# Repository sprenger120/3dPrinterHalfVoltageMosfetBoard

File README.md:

# 3D Printer Half Voltage MOSFET Board
Makes 12V Heaters (Bed + Extruder) compatible with 24V by plugging in between your 3D Printer's motherboard and your heating elements. 
The board contains **overheat protection** and will leave the heaters off regardless of what the 3D printer wants. When your printer is configured correctly a thermal runaway error should stop the machine.
The firmware also allows you to finely control how much voltage you want to send to your heaters if the 50% reduction isn't enough or you want to boost performance slightly.

### Making one

This project is mostly built from stuff I had laying around so make changes according to what you had laying around. *Capacitors with a higher voltage but the same farads rating are always compatible!*  

You can find the PCB's gerber files in fab/.

- 1x 10uF 36V MLCC , 0805 (imperial) 
- 3x 2.2uF 16V MLCC, 0603 (imperial) 
- 3x 1uF 36V MLCC, 0805 (imperial) 
- 7x 100nF 16V MLCC, 0603 (imperial) 
- 4x 100uF 35V Al-Poly Capacitor, 10x12mm
- 2x Green LED, 0603 (imperial)
- 1x ESDCAN01-2BLY TVS diode (optional if you like to live "dangerously")
- 2x Phoenix 1987740 Screw Terminal 32A (select something equivalent, these have a wierd orientation)
- 1x Phoenix 1729018 Screw Terminal 10A (or just solder wires, this is for signal only)
- 2x Vishay SiSA88DN N-Ch Enh. MOSFET
- 4x 20k Ohm Resistor, 0603 (imperial)
- 2x 300 Ohm Resistor, 0603 (imperial)
- 3x 10k Ohm Resistor, 0603 (imperial)
- 2x 10 Ohm Resistor, 0603 (imperial)
- 2x 100k Ohm Resistor, 0603 (imperial)
- 1x 10k Ohm NTC Thermistor, 0603 (imperial) (Panasonic ERT-J1VG103JA or equivalent)
- 1x STM32L011F3P Microcontroller
- 1x MCP1703A-3302 3.3V fixed linear regulator
- 1x XC6702-3.3 12V fixed linear regulator
- 1x MIC4126 MOSFET driver

Get a cheap STLINK off of ebay and hook up the pins of the J_SWD connector to it.

**todo swd port pinout**, **todo flash manual**

### Wiring 

- Connect your power supplies' 24V directly to one of the GND, 24V pairs on the left side. Connect the other GND, 24V pair to your motherboard. They are internally bridged. You may use thinner wiring for this connection as your 3D Printer's motherboard now consumes way less power. 
- Connect your heated bed to Heater1+ and Heater1- and your extruder to Heater 2+ and -. Polarity doesn't matter as heaters are just resistors. 
- Connect the **negative** side of your 3D printer's heated bed power output to "Signal Heater 1". Do the same for the extruder output and "Signal Heater 2". 

You have to connect the "Signal Heater" pins to the negative side as virtually all 3D printer motherboards don't switch the plus side but rather switch the negative side. If you would connect the the "Signal Heater" pins to the positive side the board the heaters will stay off permanently.

**todo rev. 1 testing**

### Revisions

- Rev. 2
   - Secured "Signal Heater" inputs against accidental 24V connection
- Rev. 1 (Initial release)

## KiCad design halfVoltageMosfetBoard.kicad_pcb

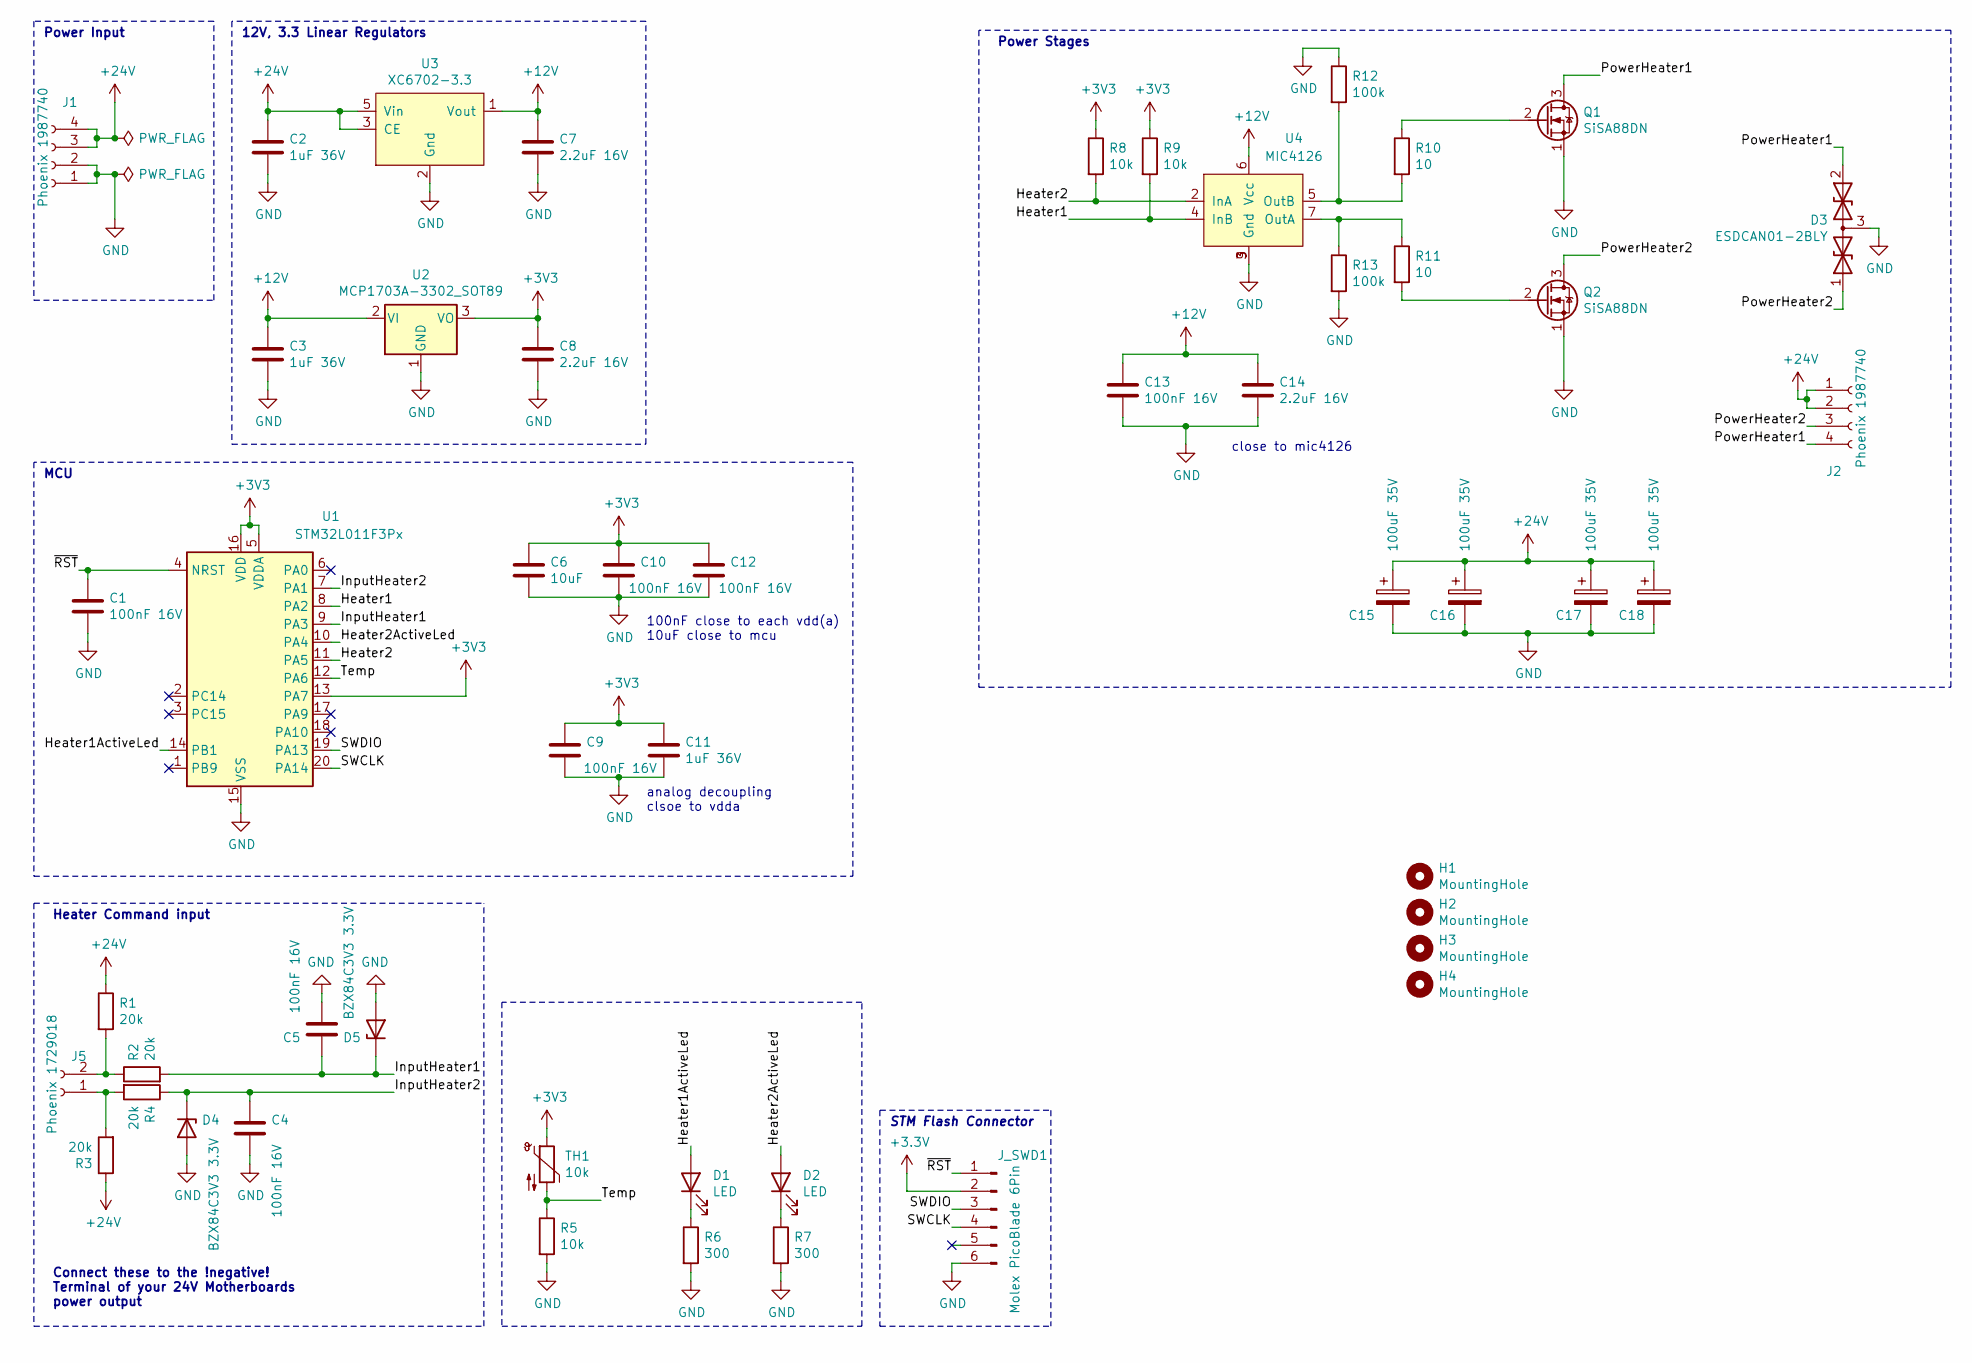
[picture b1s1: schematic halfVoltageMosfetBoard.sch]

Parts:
C1, C4, C5, C9, C10, C12, C13: 100nF 16V; C_0603_1608Metric
C2, C3, C11: 1uF 36V; C_0805_2012Metric
C6: 10uF; C_0805_2012Metric
C7, C8, C14: 2.2uF 16V; C_0603_1608Metric
C15, C16, C17, C18: 100uF 35V; CP_Elec_10x12.5
D1, D2: LED; LED_0603_1608Metric
D3: ESDCAN01-2BLY; SOT-23
D4, D5: BZX84C3V3 3.3V; D_SOT-23_ANK
H1, H2, H3, H4: MountingHole; MountingHole_3.5mm
J1, J2: Phoenix 1987740; TerminalBlock_Phoenix_PT-1,5-4-5.0-H_1x04_P5.00mm_Horizontal
J5: Phoenix 1729018; TerminalBlock_Phoenix_PT-1,5-2-5.0-H_1x02_P5.00mm_Horizontal
J_SWD1: Molex PicoBlade 6Pin; Molex_PicoBlade_53047-0610_1x06_P1.25mm_Vertical
Q1, Q2: SiSA88DN; Vishay_PowerPAK_1212-8_Single
R1, R2, R3, R4: 20k; R_0603_1608Metric
R5, R8, R9: 10k; R_0603_1608Metric
R6, R7: 300; R_0603_1608Metric
R10, R11: 10; R_0603_1608Metric
R12, R13: 100k; R_0603_1608Metric
TH1: 10k; R_0603_1608Metric
U1: STM32L011F3Px; TSSOP-20_4.4x6.5mm_P0.65mm
U2: MCP1703A-3302_SOT89; SOT-89-3
U3: XC6702-3.3; SOT-89-5
U4: MIC4126; SOIC-8-1EP_3.9x4.9mm_P1.27mm_EP2.29x3mm_ThermalVias

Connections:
+12V: C3.1, C7.1, C13.1, C14.1, U2.2 (VI), U3.1 (Vout), U4.6 (Vcc)
+24V: C2.1, C15.1, C16.1, C17.1, C18.1, J1.3, J1.4, J2.1, J2.2, R1.1, R3.1, U3.3 (CE), U3.5 (Vin)
/Heater1: R9.2, U1.8 (PA2), U4.4 (InB)
/Heater1ActiveLed: D1.2 (A), U1.14 (PB1)
/Heater2: R8.2, U1.11 (PA5), U4.2 (InA)
/Heater2ActiveLed: D2.2 (A), U1.10 (PA4)
/InputHeater1: C5.1, D5.1 (K), R2.2, U1.9 (PA3)
/InputHeater2: C4.1, D4.1 (K), R4.1, U1.7 (PA1)
/PowerHeater1: D3.2 (A2), J2.4, Q1.3 (D)
/PowerHeater2: D3.1 (A1), J2.3, Q2.3 (D)
/SWCLK: J_SWD1.4, U1.20 (PA14)
/SWDIO: J_SWD1.3, U1.19 (PA13)
/Temp: R5.1, TH1.2, U1.12 (PA6)
/~RST: C1.1, J_SWD1.1, U1.4 (NRST)
GND: C1.2, C2.2, C3.2, C4.2, C5.2, C6.2, C7.2, C8.2, C9.2, C10.2, C11.2, C12.2, C13.2, C14.2, C15.2, C16.2, C17.2, C18.2, D3.3 (common), D4.2 (A), D5.2 (A), J1.1, J1.2, J_SWD1.6, Q1.1 (S), Q2.1 (S), R5.2, R6.2, R7.2, R12.1, R13.2, U1.15 (VSS), U2.1 (GND), U3.2 (Gnd), U4.3 (Gnd), U4.9 (Gnd)
unnamed: D1.1 (K), R6.1
unnamed: D2.1 (K), R7.1
unnamed: J5.1, R3.2, R4.2
unnamed: J5.2, R1.2, R2.1
unnamed: Q1.2 (G), R10.1
unnamed: Q2.2 (G), R11.2
unnamed: R10.2, R12.2, U4.5 (OutB)
unnamed: R11.1, R13.1, U4.7 (OutA)

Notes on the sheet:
close to mic4126
STM Flash Connector
Power Input
12V, 3.3 Linear Regulators
Power Stages
analog decoupling clsoe to vdda
100nF close to each vdd(a) 10uF close to mcu
MCU
Connect these to the !negative! Terminal of your 24V Motherboards power output
Heater Command input

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
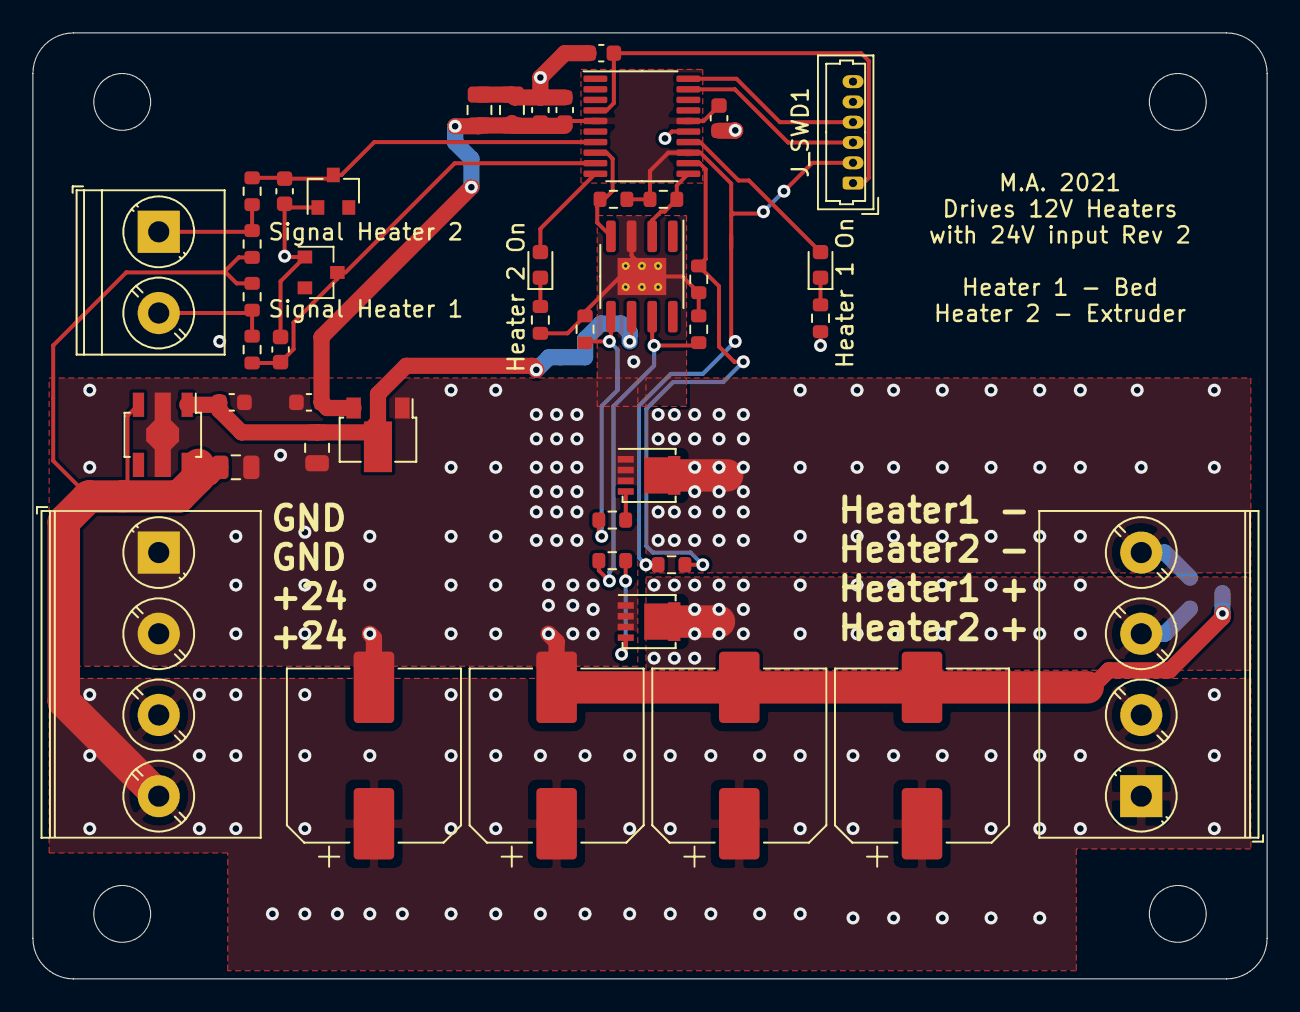
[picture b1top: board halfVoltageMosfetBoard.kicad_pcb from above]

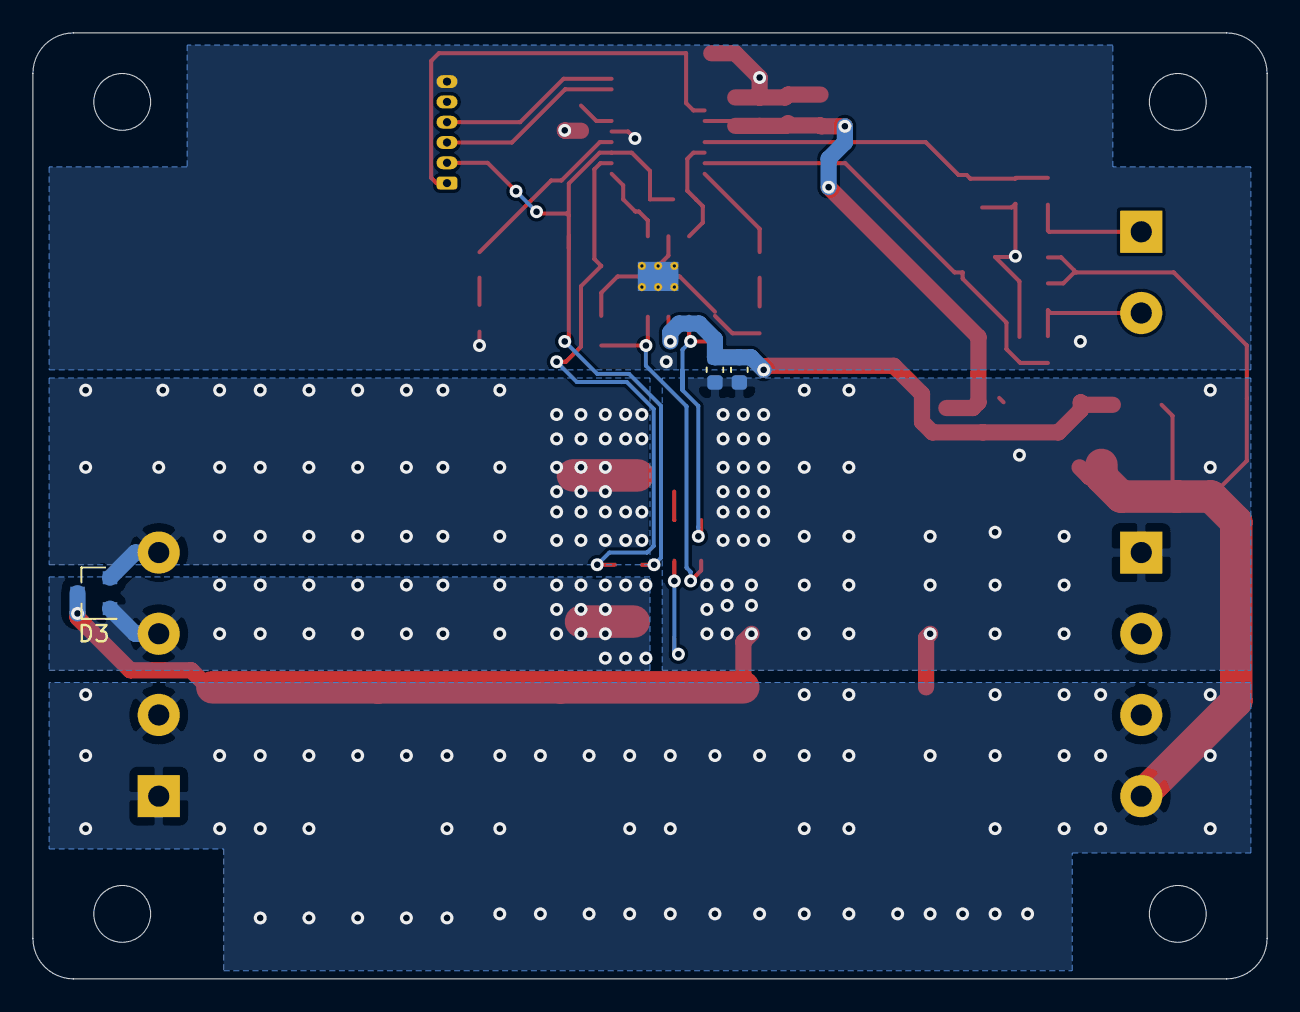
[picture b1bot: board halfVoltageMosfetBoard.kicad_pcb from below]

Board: 2 copper layers, 76.0 x 58.2 mm, 51 parts (3 on the bottom side), 24 nets.

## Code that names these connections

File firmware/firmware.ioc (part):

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Mcu.Name=STM32L011F(3-4)Px
Mcu.Package=TSSOP20
Mcu.UserName=STM32L011F3Px
PA13.Mode=Serial_Wire
PA13.Signal=SYS_SWDIO
PA14.Mode=Serial_Wire
PA14.Signal=SYS_SWCLK
PA2.Signal=S_TIM21_CH1
PA5.Signal=S_TIM2_CH1
PA6.Mode=IN6
PA6.Signal=ADC_IN6
RCC.HSE_VALUE=8000000
RCC.SYSCLKFreq_VALUE=2097000
board=custom

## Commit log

2021-05-12 finished schematic
2021-05-12 finished layout rev A
2021-05-12 Revision 2 changes see readme Added text to readme Exported schematic
2021-05-12 Added review log
2021-05-12 note about gerber files
